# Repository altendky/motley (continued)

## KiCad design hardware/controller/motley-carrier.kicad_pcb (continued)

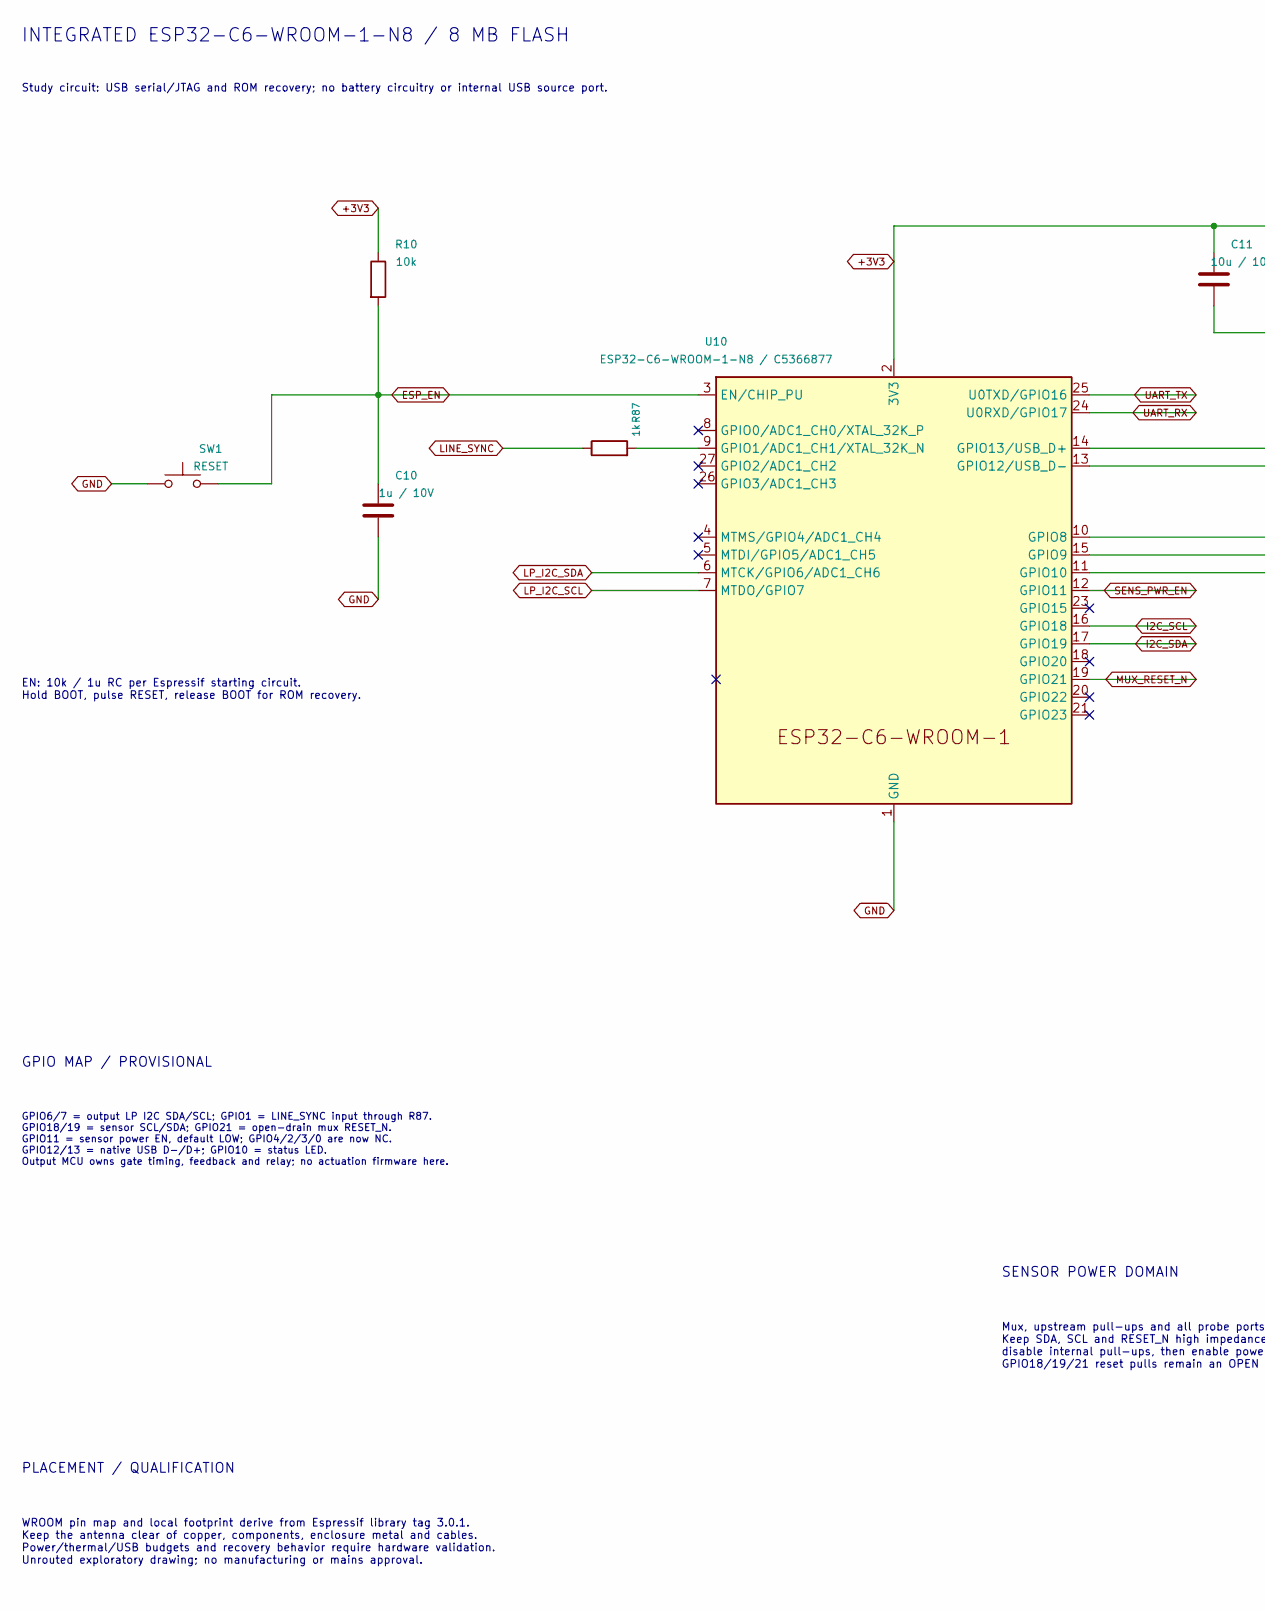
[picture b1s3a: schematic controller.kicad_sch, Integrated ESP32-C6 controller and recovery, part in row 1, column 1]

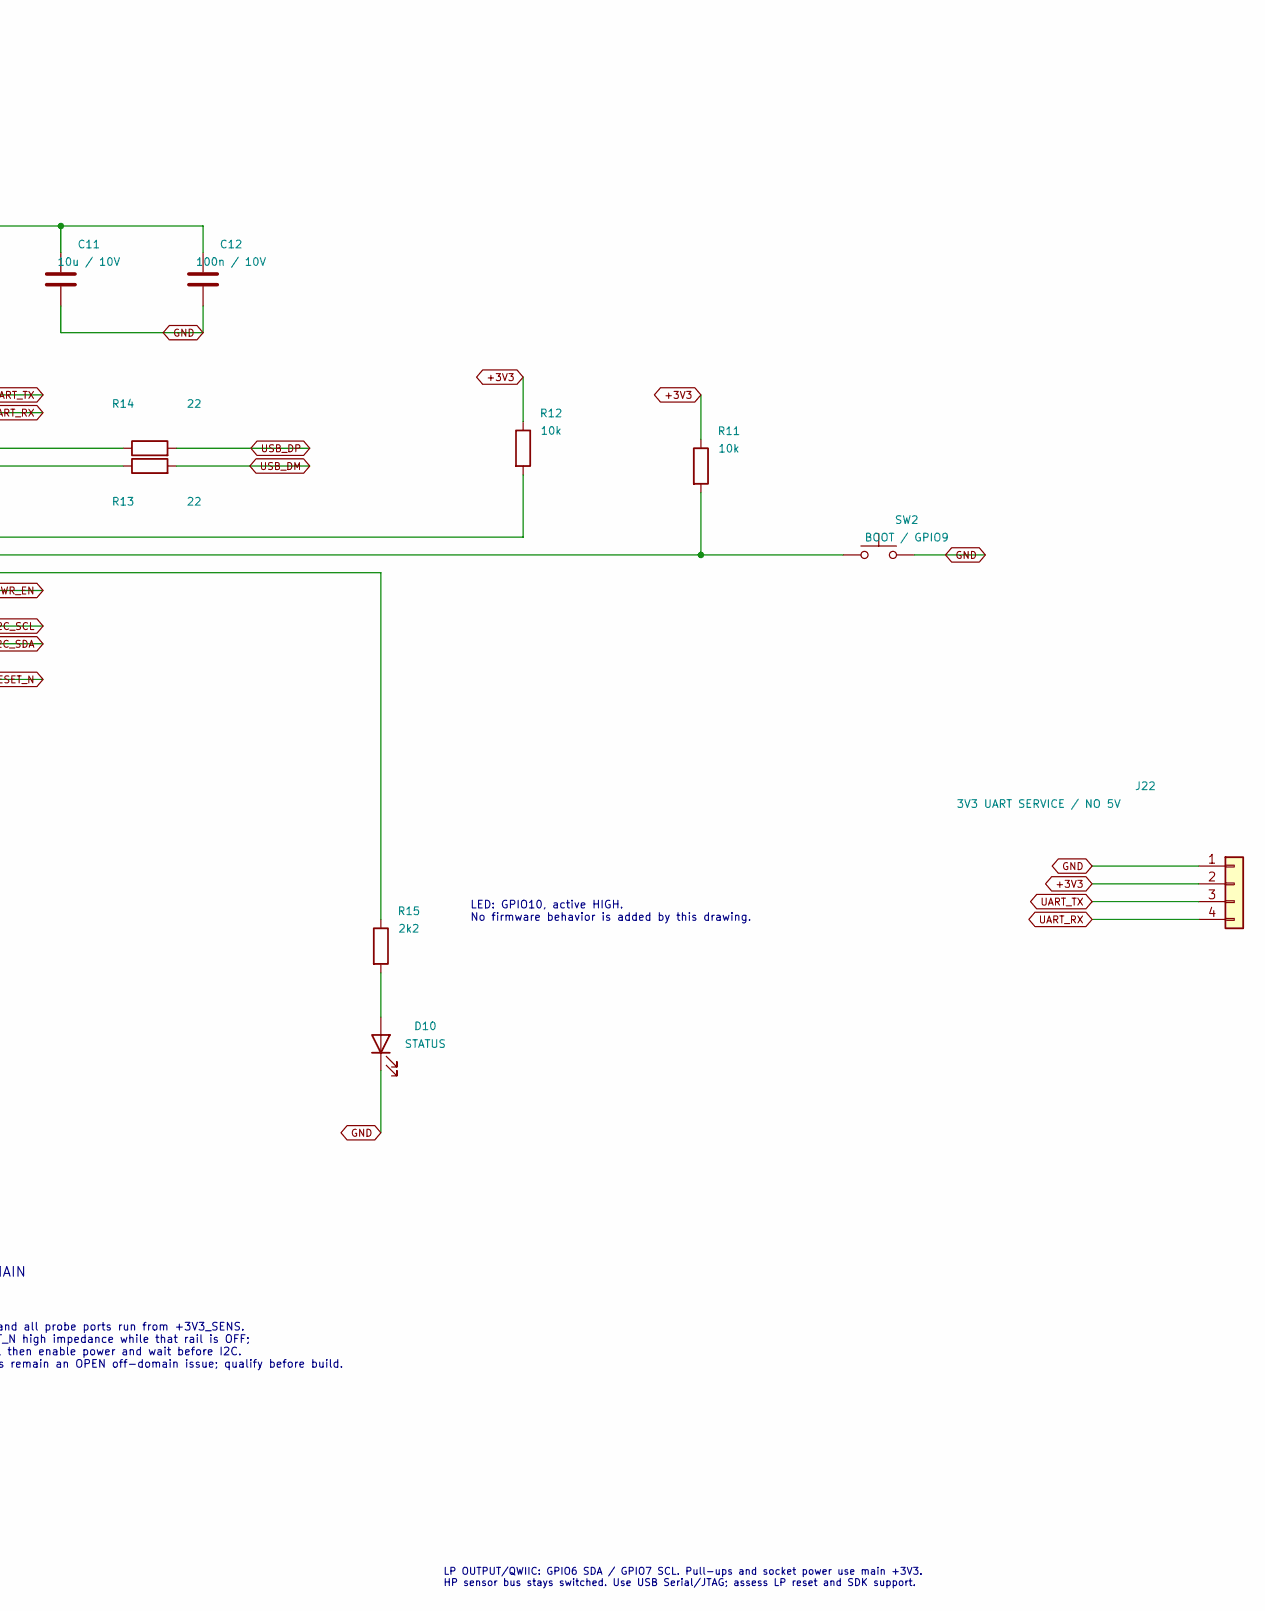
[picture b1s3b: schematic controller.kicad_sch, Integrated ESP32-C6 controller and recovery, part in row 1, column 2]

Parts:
C10: 1u / 10V; C_0805_2012Metric
C11: 10u / 10V; C_0805_2012Metric
C12: 100n / 10V; C_0805_2012Metric
D10: STATUS; LED_0805_2012Metric
J22: 3V3 UART SERVICE / NO 5V; PinHeader_1x04_P2.54mm_Vertical
R10, R11, R12: 10k; R_0805_2012Metric
R13, R14: 22; R_0805_2012Metric
R15: 2k2; R_0805_2012Metric
R87: 1k; R_0805_2012Metric
SW1: RESET; SW_SPST_TL3305A
SW2: BOOT / GPIO9; SW_SPST_TL3305A
U10: ESP32-C6-WROOM-1-N8 / C5366877; ESP32-C6-WROOM-1

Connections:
+3V3: C11.1, C12.1, J22.2, R10.1, R11.1, R12.1, U10.2 (3V3); also elsewhere on the board
ESP_EN: C10.1, R10.2, SW1.2, U10.3 (EN/CHIP_PU)
GND: C10.2, C11.2, C12.2, D10.1 (K), J22.1, SW1.1, SW2.2, U10.1 (GND), U10.28 (GND), U10.29 (GND); also elsewhere on the board
I2C_SCL: U10.16 (GPIO18); also elsewhere on the board
I2C_SDA: U10.17 (GPIO19); also elsewhere on the board
LINE_SYNC: R87.1; also elsewhere on the board
LP_I2C_SCL: U10.7 (MTDO/GPIO7); also elsewhere on the board
LP_I2C_SDA: U10.6 (MTCK/GPIO6/ADC1_CH6); also elsewhere on the board
MUX_RESET_N: U10.19 (GPIO21); also elsewhere on the board
unnamed: D10.2 (A), R15.2
unnamed: R87.2, U10.9 (GPIO1/ADC1_CH1/XTAL_32K_N)
unnamed: R12.2, U10.10 (GPIO8)
unnamed: R11.2, SW2.1, U10.15 (GPIO9)
unnamed: R15.1, U10.11 (GPIO10)
unnamed: R13.1, U10.13 (GPIO12/USB_D-)
unnamed: R14.1, U10.14 (GPIO13/USB_D+)
SENS_PWR_EN: U10.12 (GPIO11); also elsewhere on the board
UART_RX: J22.4, U10.24 (U0RXD/GPIO17); also elsewhere on the board
UART_TX: J22.3, U10.25 (U0TXD/GPIO16); also elsewhere on the board
USB_DM: R13.2; also elsewhere on the board
USB_DP: R14.2; also elsewhere on the board

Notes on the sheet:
LED: GPIO10, active HIGH. No firmware behavior is added by this drawing.
PLACEMENT / QUALIFICATION
EN: 10k / 1u RC per Espressif starting circuit. Hold BOOT, pulse RESET, release BOOT for ROM recovery.
Mux, upstream pull-ups and all probe ports run from +3V3_SENS. Keep SDA, SCL and RESET_N high impedance while that rail is OFF; disable internal pull-ups, then enable power and wait before I2C. GPIO18/19/21 reset pulls remain an OPEN off-domain issue; qualify before build.
GPIO6/7 = output LP I2C SDA/SCL; GPIO1 = LINE_SYNC input through R87. GPIO18/19 = sensor SCL/SDA; GPIO21 = open-drain mux RESET_N. GPIO11 = sensor power EN, default LOW; GPIO4/2/3/0 are now NC. GPIO12/13 = native USB D-/D+; GPIO10 = status LED. Output MCU owns gate timing, feedback and relay; no ac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
GPIO MAP / PROVISIONAL
SENSOR POWER DOMAIN
LP OUTPUT/QWIIC: GPIO6 SDA / GPIO7 SCL. Pull-ups and socket power use main +3V3. HP sensor bus stays switched. Use USB Serial/JTAG; assess LP reset and SDK support.
INTEGRATED ESP32-C6-WROOM-1-N8 / 8 MB FLASH
Study circuit: USB serial/JTAG and ROM recovery; no battery circuitry or internal USB source port.
WROOM pin map and local footprint derive from Espressif library tag 3.0.1. Keep the antenna clear of copper, components, enclosure metal and cables. Power/thermal/USB budgets and recovery behavior require hardware validation. Unrouted exploratory drawing; no manufacturing or mains approval.

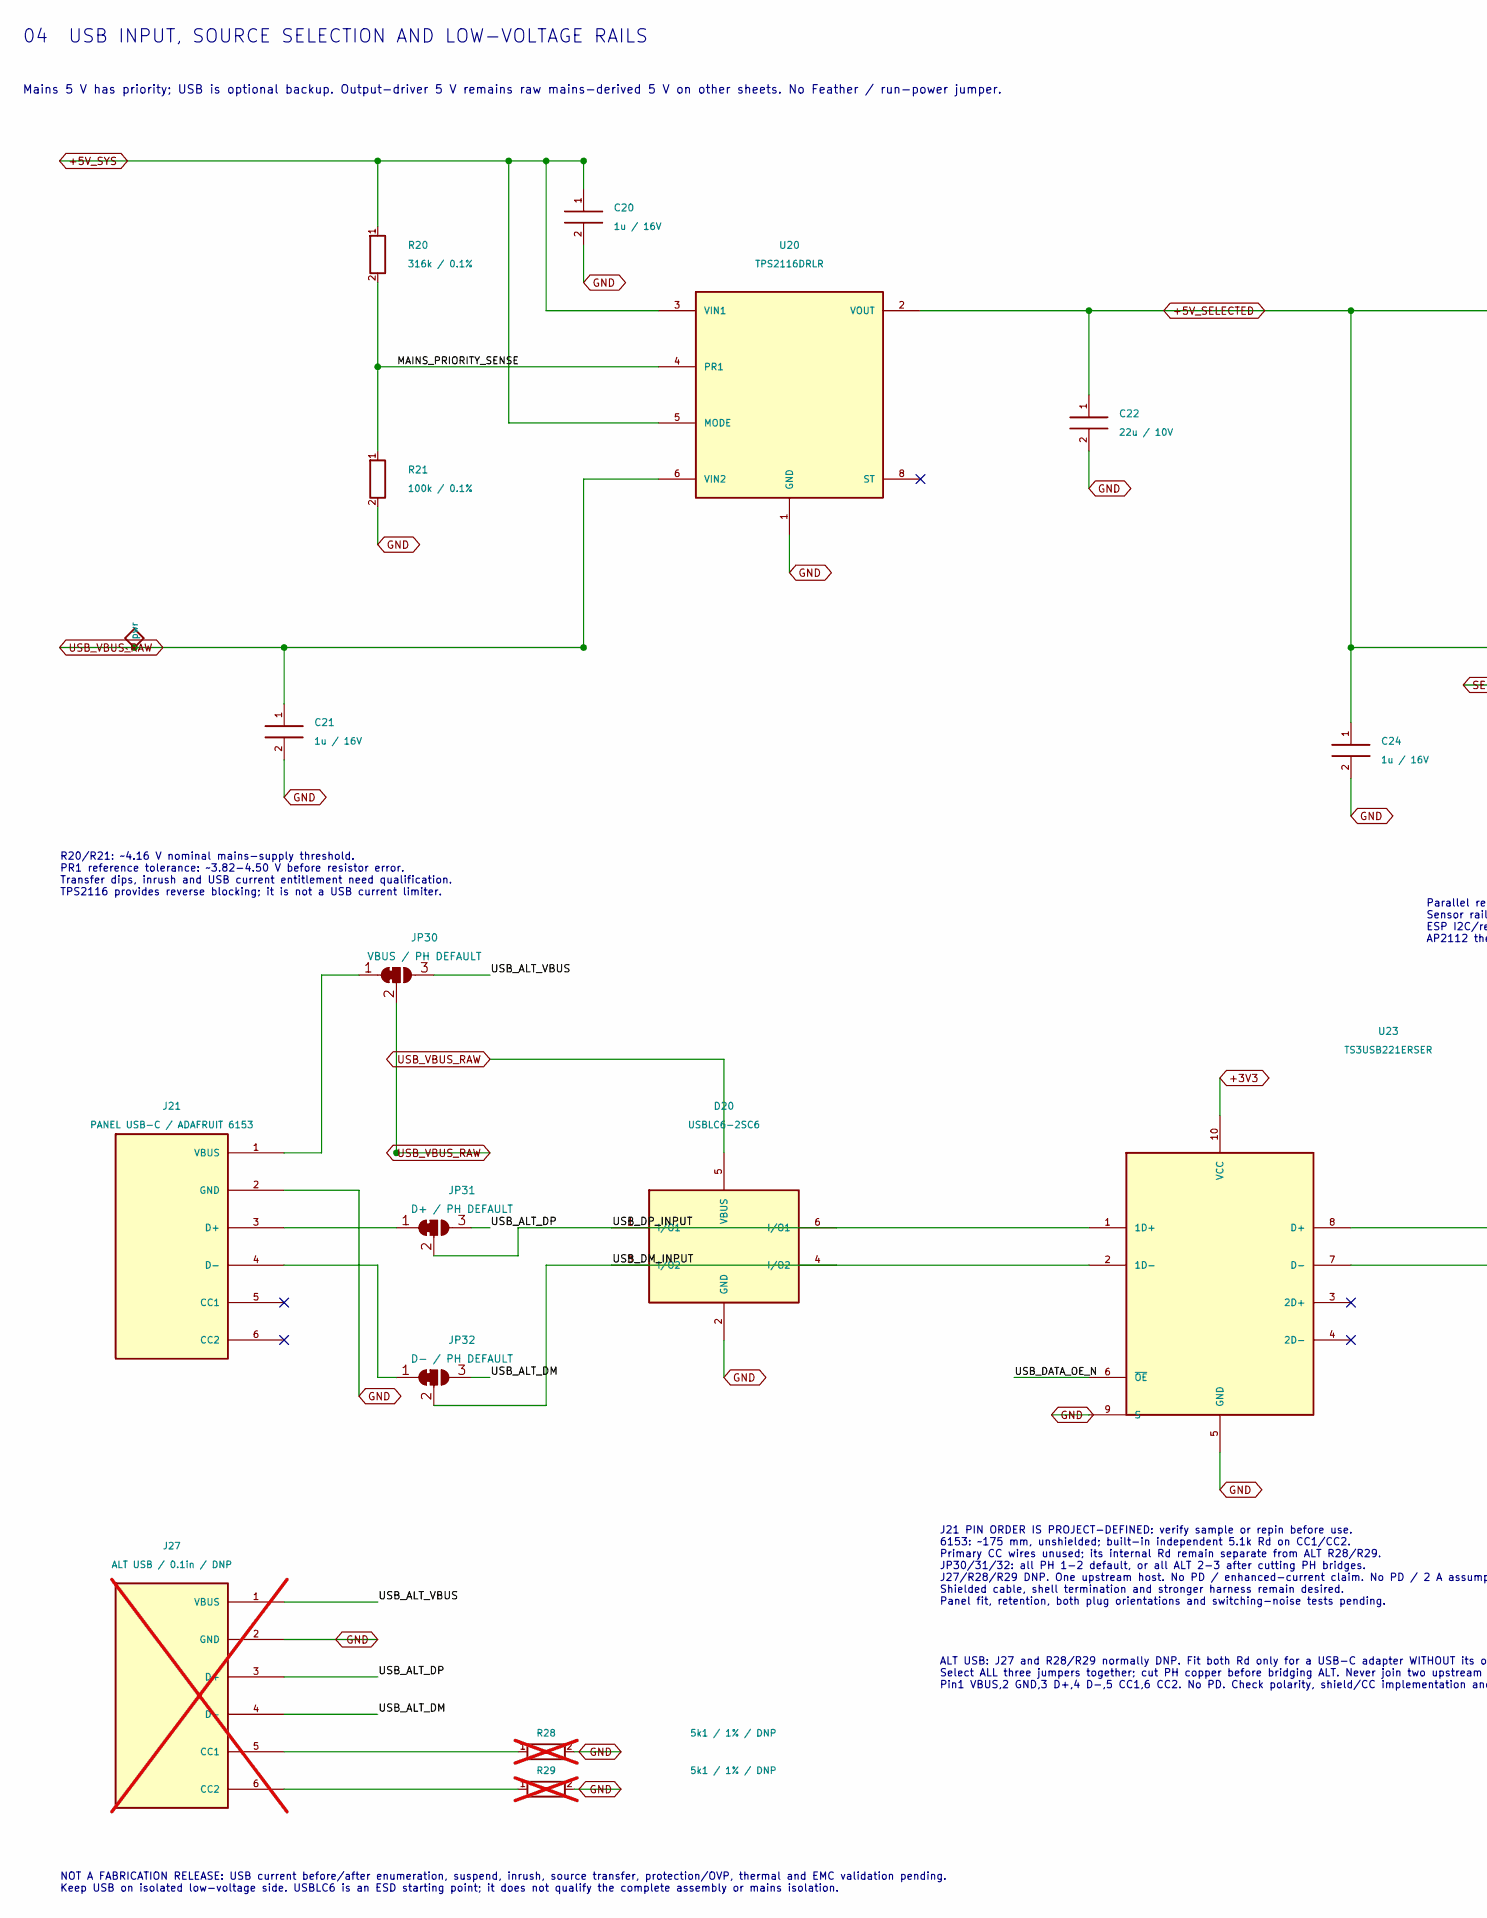
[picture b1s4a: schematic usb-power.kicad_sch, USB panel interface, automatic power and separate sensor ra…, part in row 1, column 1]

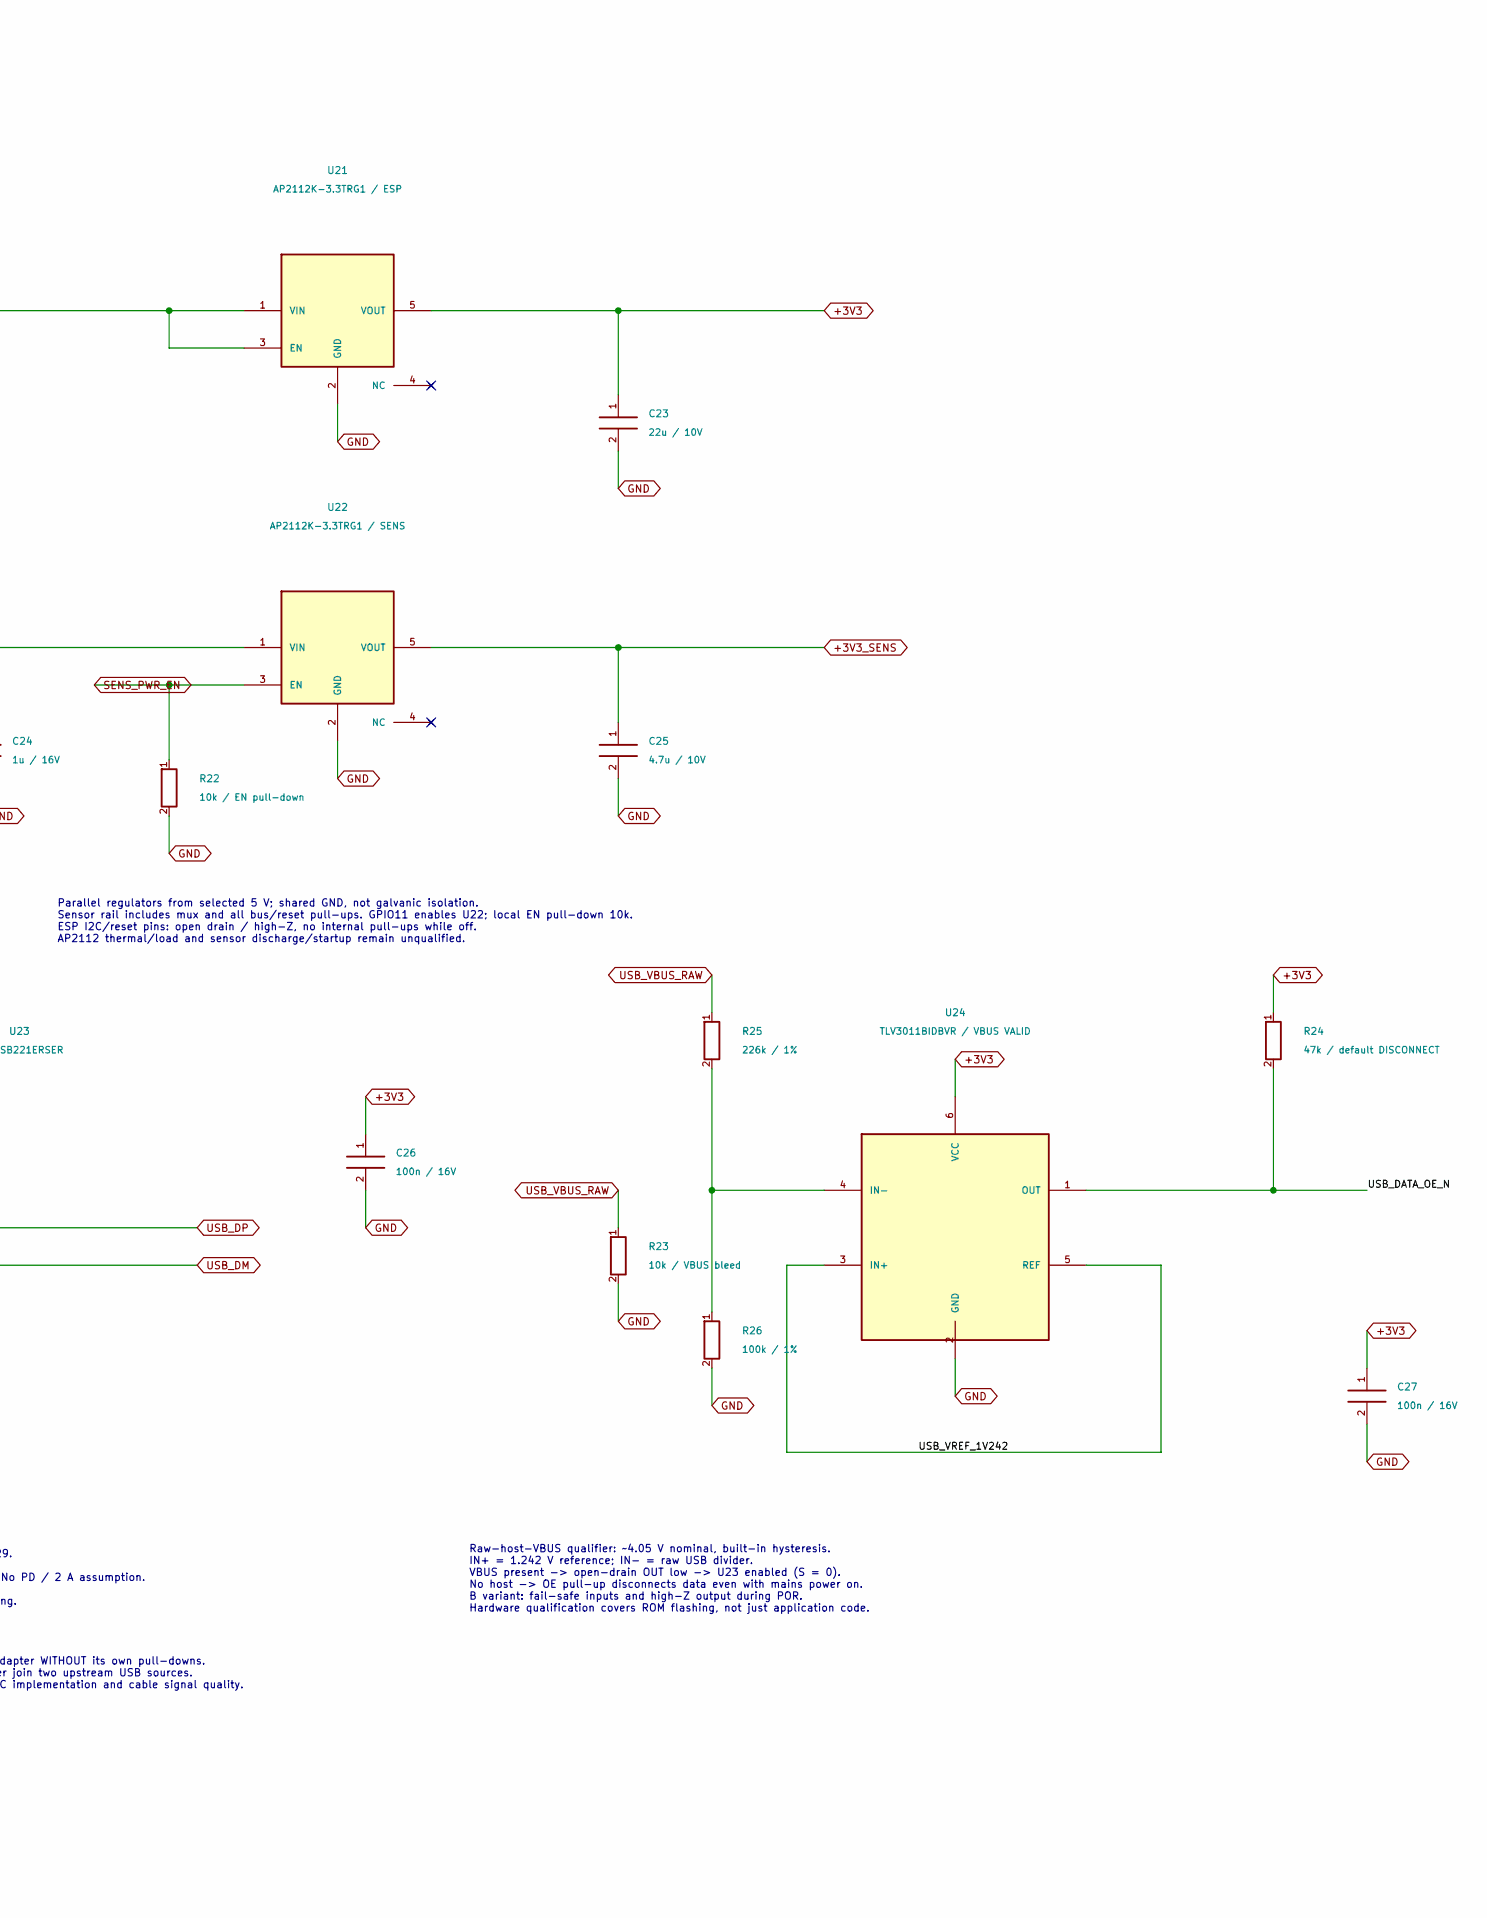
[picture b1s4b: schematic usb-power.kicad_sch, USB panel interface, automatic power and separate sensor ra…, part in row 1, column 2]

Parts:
C20, C21, C24: 1u / 16V; C_0603_1608Metric
C22, C23: 22u / 10V; C_0805_2012Metric
C25: 4.7u / 10V; C_0603_1608Metric
C26, C27: 100n / 16V; C_0603_1608Metric
D20: USBLC6-2SC6; SOT-23-6
J21: PANEL USB-C / ADAFRUIT 6153; JST_PH_B6B-PH-K_1x06_P2.00mm_Vertical
J27: ALT USB / 0.1in / DNP; PinHeader_1x06_P2.54mm_Vertical; not fitted
JP30: VBUS / PH DEFAULT; SolderJumper-3_P1.3mm_Bridged12_RoundedPad1.0x1.5mm
JP31: D+ / PH DEFAULT; SolderJumper-3_P1.3mm_Bridged12_RoundedPad1.0x1.5mm
JP32: D- / PH DEFAULT; SolderJumper-3_P1.3mm_Bridged12_RoundedPad1.0x1.5mm
R20: 316k / 0.1%; R_0603_1608Metric
R21: 100k / 0.1%; R_0603_1608Metric
R22: 10k / EN pull-down; R_0603_1608Metric
R23: 10k / VBUS bleed; R_0603_1608Metric
R24: 47k / default DISCONNECT; R_0603_1608Metric
R25: 226k / 1%; R_0603_1608Metric; MPN AC0603FR-07226KL; LCSC C227714
R26: 100k / 1%; R_0603_1608Metric
R28, R29: 5k1 / 1% / DNP; R_0603_1608Metric; not fitted
U20: TPS2116DRLR; SOT-583-8
U21: AP2112K-3.3TRG1 / ESP; SOT-23-5
U22: AP2112K-3.3TRG1 / SENS; SOT-23-5
U23: TS3USB221ERSER; Texas_UQFN-10_1.5x2mm_P0.5mm
U24: TLV3011BIDBVR / VBUS VALID; SOT-23-6

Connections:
+3V3: C23.1, C26.1, C27.1, R24.1, U21.5 (VOUT), U23.10 (VCC), U24.6 (VCC); also elsewhere on the board
+3V3_SENS: C25.1, U22.5 (VOUT); also elsewhere on the board
+5V_SELECTED: C22.1, C24.1, U20.2 (VOUT), U20.7 (VOUT), U21.1 (VIN), U21.3 (EN), U22.1 (VIN); also elsewhere on the board
+5V_SYS: C20.1, R20.1, U20.3 (VIN1), U20.5 (MODE); also elsewhere on the board
/USB input, source selection and 3V3 rails/MAINS_PRIORITY_SENSE: R20.2, R21.1, U20.4 (PR1)
/USB input, source selection and 3V3 rails/USB_ALT_DM: J27.4 (D-), JP32.3 (B)
/USB input, source selection and 3V3 rails/USB_ALT_DP: J27.3 (D+), JP31.3 (B)
/USB input, source selection and 3V3 rails/USB_ALT_VBUS: J27.1 (VBUS), JP30.3 (B)
/USB input, source selection and 3V3 rails/USB_DATA_OE_N: R24.2, U23.6 (~OE), U24.1 (OUT)
/USB input, source selection and 3V3 rails/USB_DM_INPUT: D20.3 (I/O2), D20.4 (I/O2), JP32.2 (C), U23.2 (1D-)
/USB input, source selection and 3V3 rails/USB_DP_INPUT: D20.1 (I/O1), D20.6 (I/O1), JP31.2 (C), U23.1 (1D+)
/USB input, source selection and 3V3 rails/USB_VREF_1V242: U24.3 (IN+), U24.5 (REF)
GND: C20.2, C21.2, C22.2, C23.2, C24.2, C25.2, C26.2, C27.2, D20.2 (GND), J21.2 (GND), J27.2 (GND), R21.2, R22.2, R23.2, R26.2, R28.2, R29.2, U20.1 (GND), U21.2 (GND), U22.2 (GND), U23.5 (GND), U23.9 (S), U24.2 (GND); also elsewhere on the board
unnamed: J21.3 (D+), JP31.1 (A)
unnamed: J21.4 (D-), JP32.1 (A)
unnamed: J21.1 (VBUS), JP30.1 (A)
unnamed: J27.5 (CC1), R28.1
unnamed: J27.6 (CC2), R29.1
unnamed: R25.2, R26.1, U24.4 (IN-)
SENS_PWR_EN: R22.1, U22.3 (EN); also elsewhere on the board
USB_DM: U23.7 (D-); also elsewhere on the board
USB_DP: U23.8 (D+); also elsewhere on the board
USB_VBUS_RAW: C21.1, D20.5 (VBUS), JP30.2 (C), R23.1, R25.1, U20.6 (VIN2); also elsewhere on the board

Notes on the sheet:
Parallel regulators from selected 5 V; shared GND, not galvanic isolation. Sensor rail includes mux and all bus/reset pull-ups. GPIO11 enables U22; local EN pull-down 10k. ESP I2C/reset pins: open drain / high-Z, no internal pull-ups while off. AP2112 thermal/load and sensor discharge/startup remai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
Mains 5 V has priority; USB is optional backup. Output-driver 5 V remains raw mains-derived 5 V on other sheets. No Feather / run-power jumper.
NOT A FABRICATION RELEASE: USB current before/after enumeration, suspend, inrush, source transfer, protection/OVP, thermal and EMC validation pending. Keep USB on isolated low-voltage side. USBLC6 is an ESD starting point; it does not qualify the complete assembly or mains isolation.
R20/R21: ~4.16 V nominal mains-supply threshold. PR1 reference tolerance: ~3.82-4.50 V before resistor error. Transfer dips, inrush and USB current entitlement need qualification. TPS2116 provides reverse blocking; it is not a USB current limiter.
04 USB INPUT, SOURCE SELECTION AND LOW-VOLTAGE RAILS
J21 PIN ORDER IS PROJECT-DEFINED: verify sample or repin before use. 6153: ~175 mm, unshielded; built-in independent 5.1k Rd on CC1/CC2. Primary CC wires unused; its internal Rd remain separate from ALT R28/R29. JP30/31/32: all PH 1-2 default, or all ALT 2-3 after cutting PH bridges. J27/R28/R29 DN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
Raw-host-VBUS qualifier: ~4.05 V nominal, built-in hysteresis. IN+ = 1.242 V reference; IN- = raw USB divider. VBUS present -> open-drain OUT low -> U23 enabled (S = 0). No host -> OE pull-up disconnects data even with mains power on. B variant: fail-safe inputs and high-Z output during POR. Hardwa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
ALT USB: J27 and R28/R29 normally DNP. Fit both Rd only for a USB-C adapter WITHOUT its own pull-downs. Select ALL three jumpers together; cut PH copper before bridging ALT. Never join two upstream USB sources. Pin1 VBUS,2 GND,3 D+,4 D-,5 CC1,6 CC2. No PD. Check polarity, shield/CC implementation a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

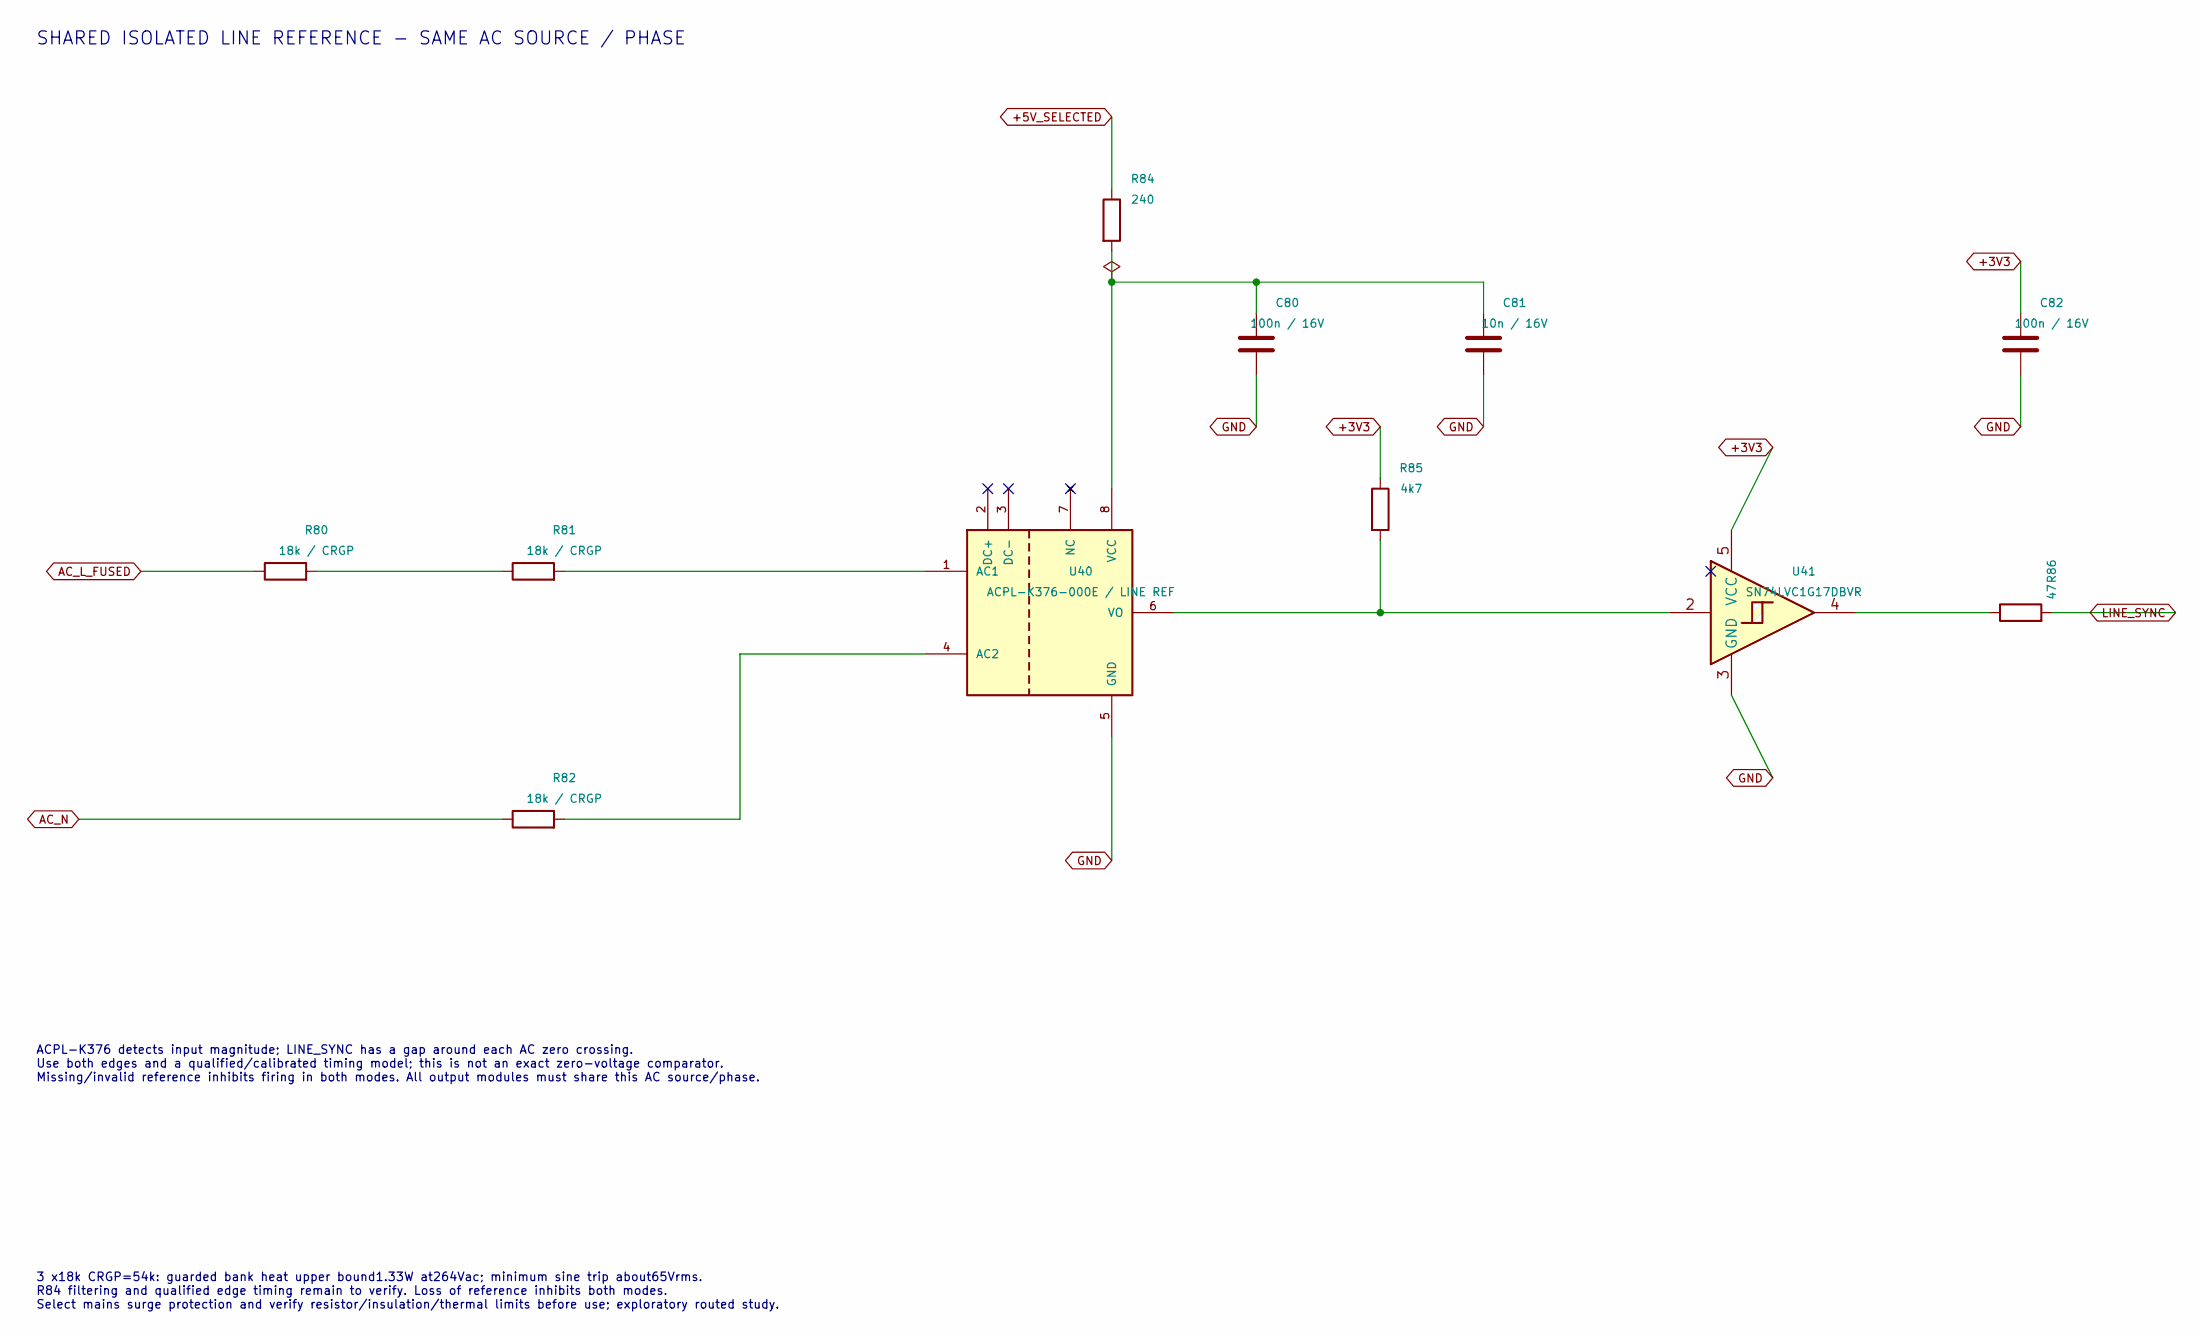
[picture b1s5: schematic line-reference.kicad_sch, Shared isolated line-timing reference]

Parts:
C80, C82: 100n / 16V; C_0805_2012Metric
C81: 10n / 16V; C_0805_2012Metric
R80, R81, R82: 18k / CRGP; R_2512_6332Metric; Rating 2W at70C /1% /500V working; qualify act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; MPN CRGP2512F18K; LCSC C2082909
R84: 240; R_0805_2012Metric
R85: 4k7; R_0805_2012Metric
R86: 47; R_0805_2012Metric
U40: ACPL-K376-000E / LINE REF; ACPL_K37x_SSO8_Study
U41: SN74LVC1G17DBVR; SOT-23-5

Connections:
+3V3: C82.1, R85.1, U41.5 (VCC); also elsewhere on the board
+5V_SELECTED: R84.1; also elsewhere on the board
AC_L_FUSED: R80.1; also elsewhere on the board
AC_N: R82.1; also elsewhere on the board
GND: C80.2, C81.2, C82.2, U40.5 (GND), U41.3 (GND); also elsewhere on the board
LINE_SYNC: R86.2; also elsewhere on the board
unnamed: R80.2, R81.1
unnamed: R86.1, U41.4
unnamed: R81.2, U40.1 (AC1)
unnamed: R82.2, U40.4 (AC2)
unnamed: C80.1, C81.1, R84.2, U40.8 (VCC)
unnamed: R85.2, U40.6 (VO), U41.2

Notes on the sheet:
ACPL-K376 detects input magnitude; LINE_SYNC has a gap around each AC zero crossing. Use both edges and a qualified/calibrated timing model; this is not an exact zero-voltage comparator. Missing/invalid reference inhibits firing in both modes. All output modules must share this AC source/phase.
SHARED ISOLATED LINE REFERENCE - SAME AC SOURCE / PHASE
3 x18k CRGP=54k: guarded bank heat upper bound1.33W at264Vac; minimum sine trip about65Vrms. R84 filtering and qualified edge timing remain to verify. Loss of reference inhibits both modes. Select mains surge protection and verify resistor/insulation/thermal limits before use; exploratory routed st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

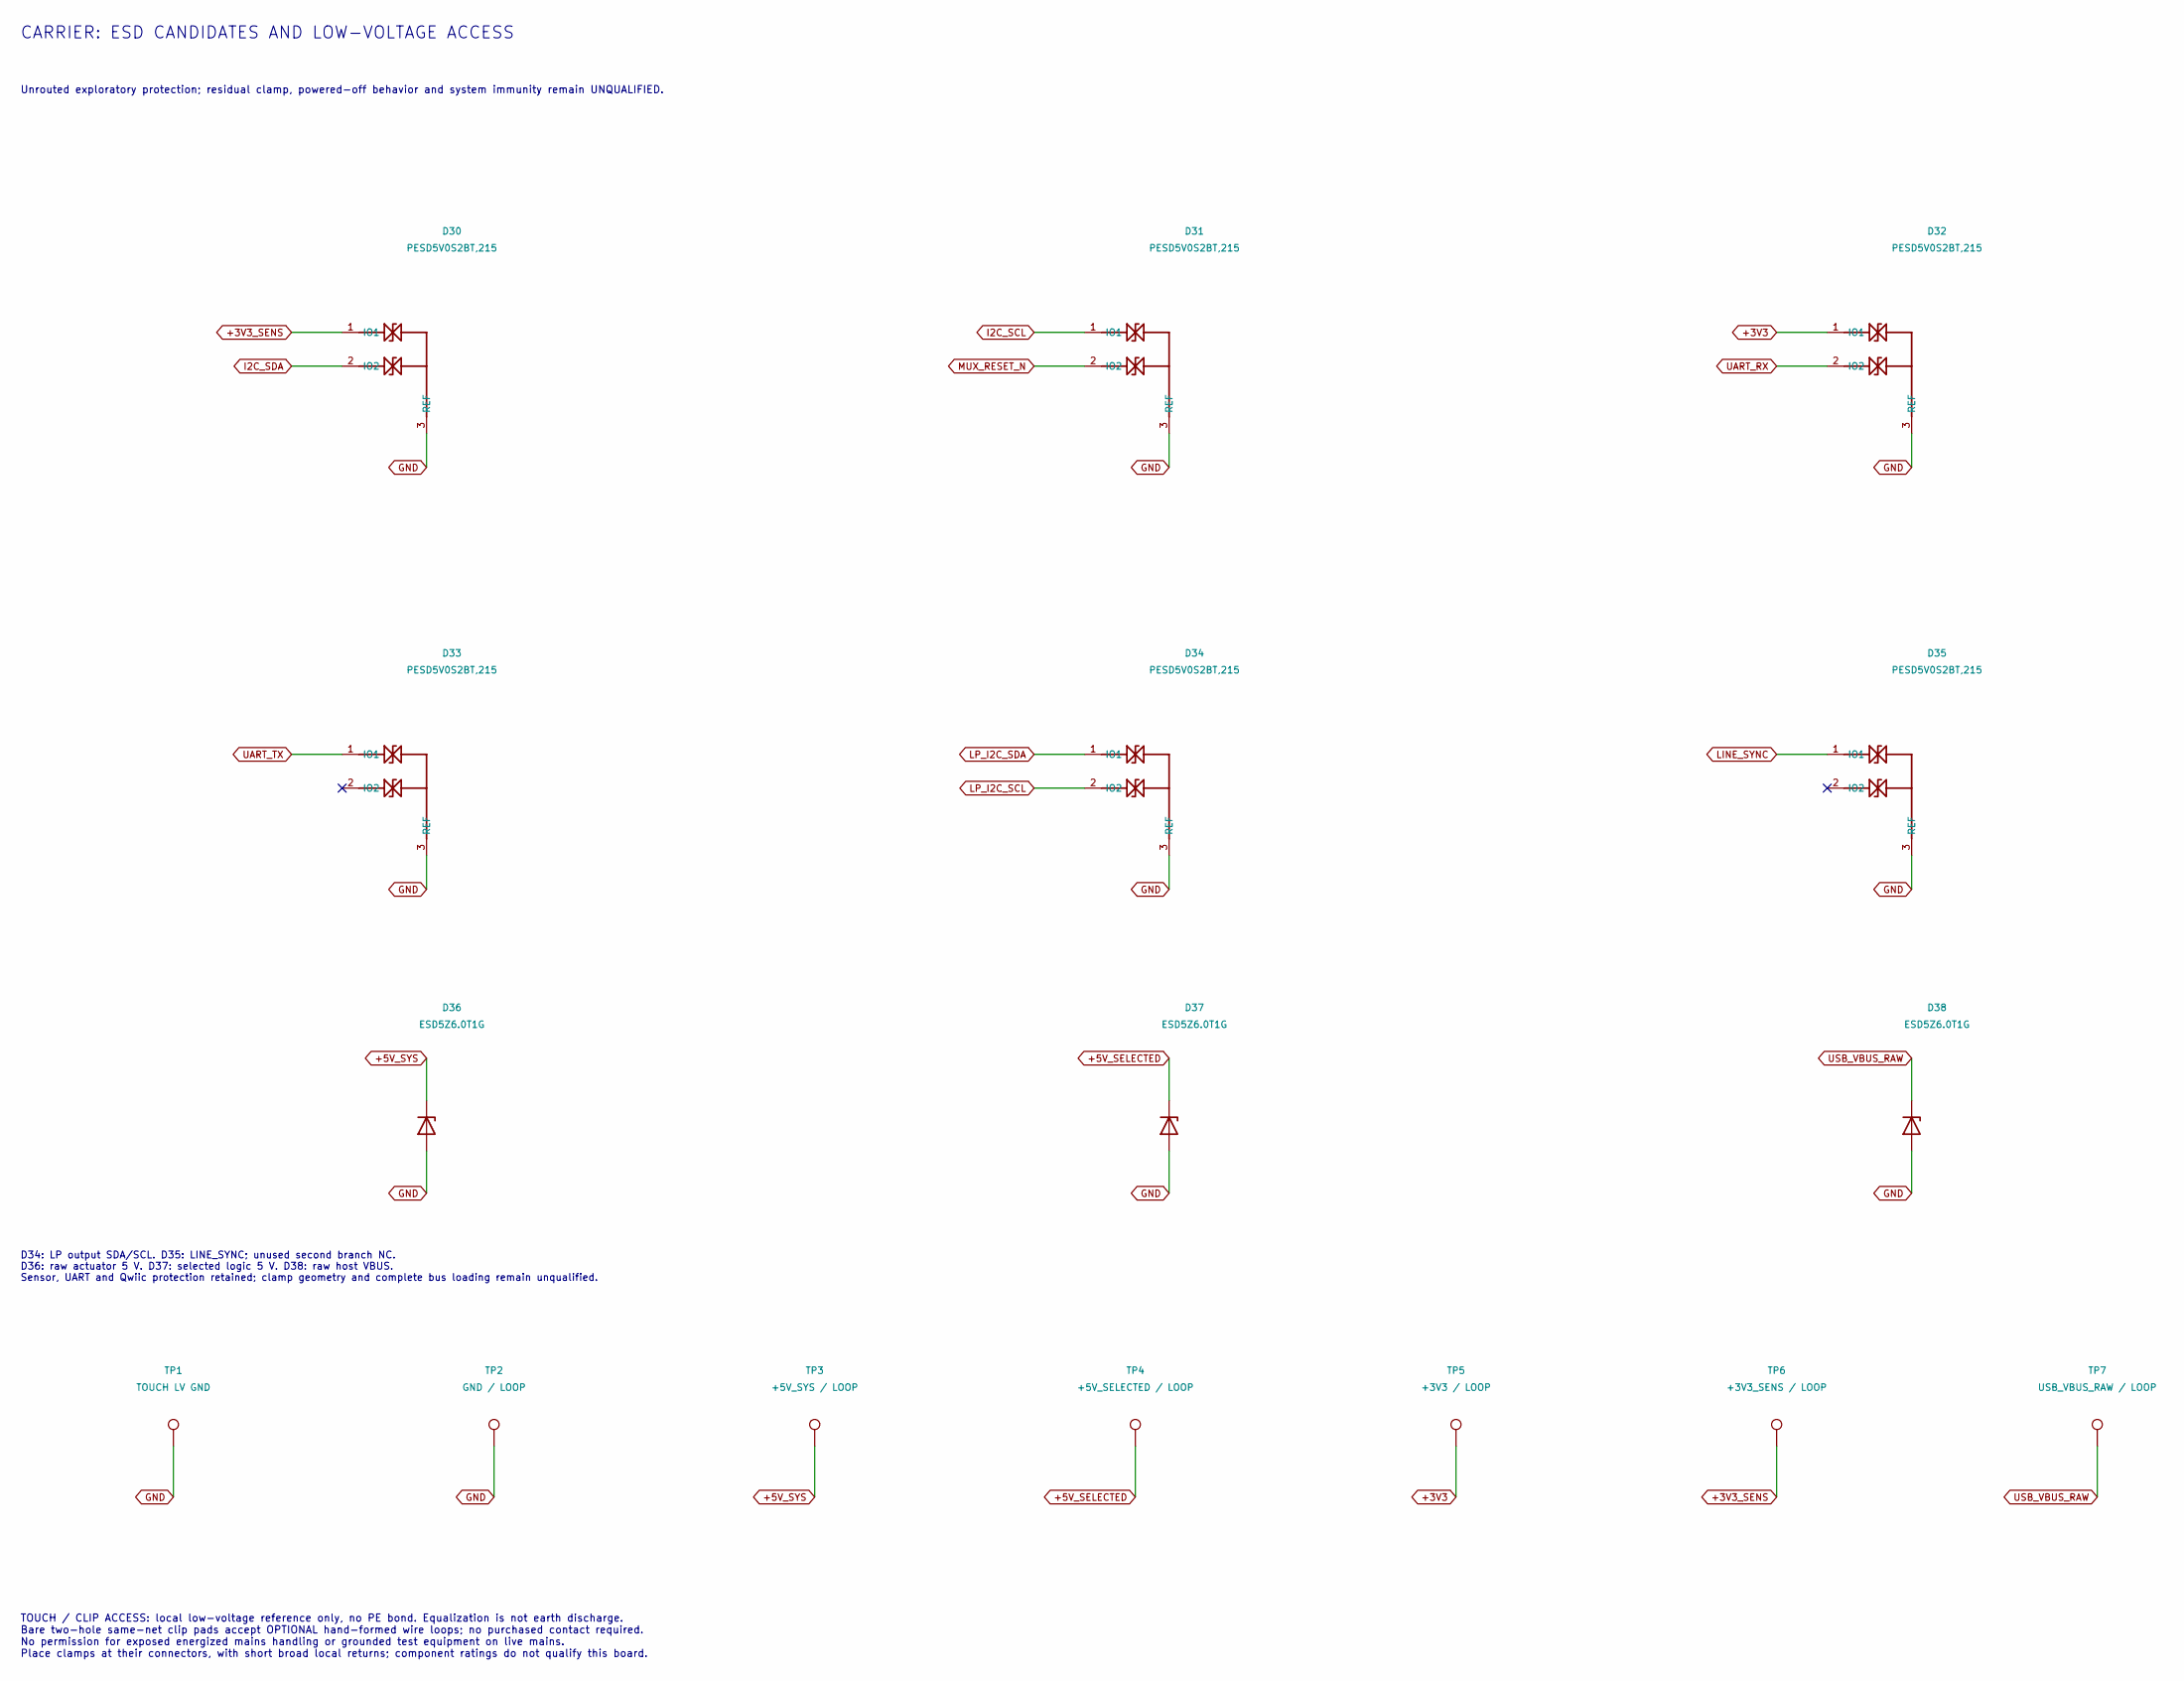
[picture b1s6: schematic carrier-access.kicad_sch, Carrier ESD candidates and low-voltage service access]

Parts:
D30, D31, D32, D33, D34, D35: PESD5V0S2BT,215; SOT-23
D36, D37, D38: ESD5Z6.0T1G; D_SOD-523
TP1: TOUCH LV GND; TouchGround_8mm
TP2: GND / LOOP; WireLoop_P2.54
TP3: +5V_SYS / LOOP; WireLoop_P2.54
TP4: +5V_SELECTED / LOOP; WireLoop_P2.54
TP5: +3V3 / LOOP; WireLoop_P2.54
TP6: +3V3_SENS / LOOP; WireLoop_P2.54
TP7: USB_VBUS_RAW / LOOP; WireLoop_P2.54

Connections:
+3V3: D32.1 (IO1), TP5.1; also elsewhere on the board
+3V3_SENS: D30.1 (IO1), TP6.1; also elsewhere on the board
+5V_SELECTED: D37.1 (K), TP4.1; also elsewhere on the board
+5V_SYS: D36.1 (K), TP3.1; also elsewhere on the board
GND: D30.3 (REF), D31.3 (REF), D32.3 (REF), D33.3 (REF), D34.3 (REF), D35.3 (REF), D36.2 (A), D37.2 (A), D38.2 (A), TP1.1, TP2.1; also elsewhere on the board
I2C_SCL: D31.1 (IO1); also elsewhere on the board
I2C_SDA: D30.2 (IO2); also elsewhere on the board
LINE_SYNC: D35.1 (IO1); also elsewhere on the board
LP_I2C_SCL: D34.2 (IO2); also elsewhere on the board
LP_I2C_SDA: D34.1 (IO1); also elsewhere on the board
MUX_RESET_N: D31.2 (IO2); also elsewhere on the board
UART_RX: D32.2 (IO2); also elsewhere on the board
UART_TX: D33.1 (IO1); also elsewhere on the board
USB_VBUS_RAW: D38.1 (K), TP7.1; also elsewhere on the board

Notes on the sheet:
Unrouted exploratory protection; residual clamp, powered-off behavior and system immunity remain UNQUALIFIED.
CARRIER: ESD CANDIDATES AND LOW-VOLTAGE ACCESS
TOUCH / CLIP ACCESS: local low-voltage reference only, no PE bond. Equalization is not earth discharge. Bare two-hole same-net clip pads accept OPTIONAL hand-formed wire loops; no purchased contact required. No permission for exposed energized mains handling or grounded test equipment on live mains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
D34: LP output SDA/SCL. D35: LINE_SYNC; unused second branch NC. D36: raw actuator 5 V. D37: selected logic 5 V. D38: raw host VBUS. Sensor, UART and Qwiic protection retained; clamp geometry and complete bus loading remain unqualified.
